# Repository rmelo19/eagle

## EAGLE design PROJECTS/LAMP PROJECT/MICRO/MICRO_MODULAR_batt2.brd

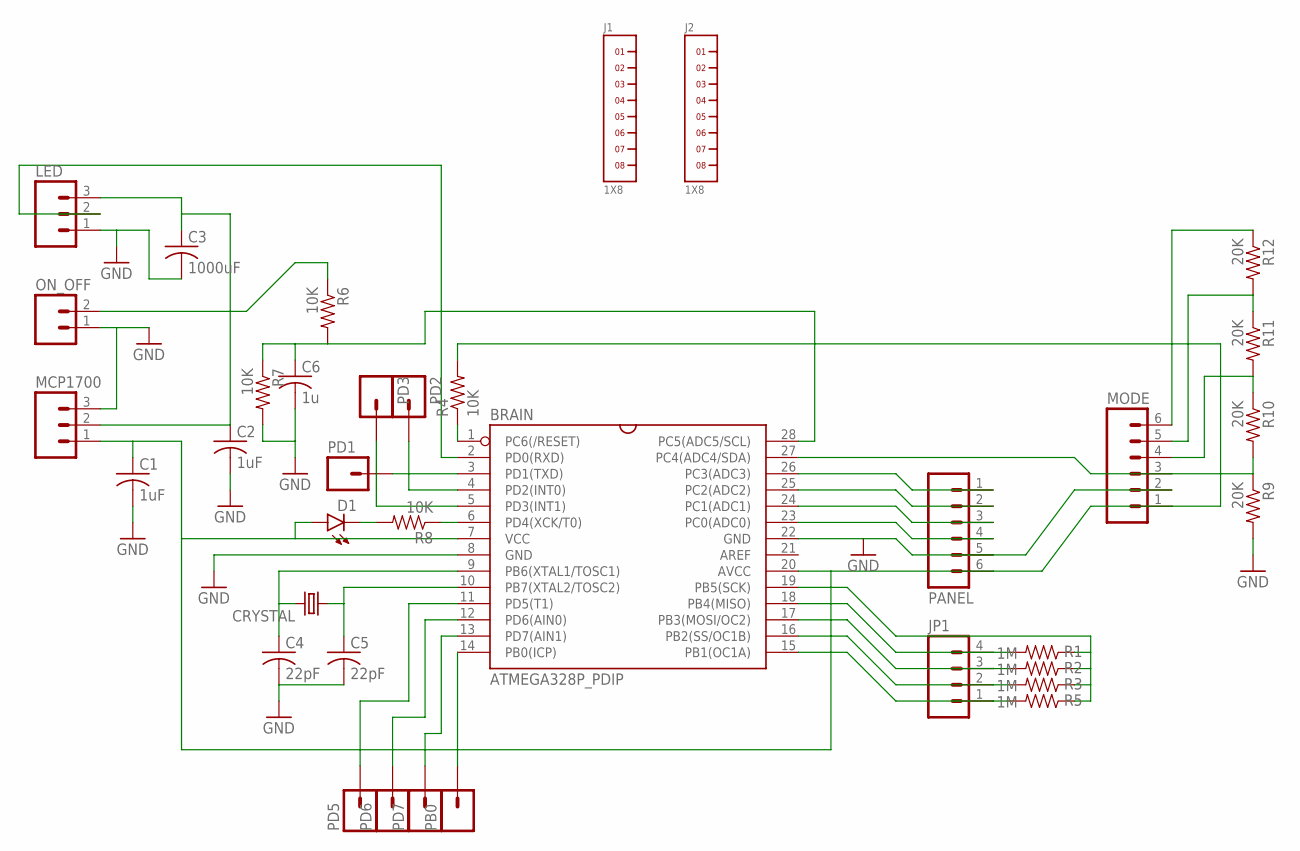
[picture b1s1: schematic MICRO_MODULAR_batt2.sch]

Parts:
BRAIN: ATMEGA328P_PDIP; DIL-28-3
C1, C2: 1uF; C050-025X075
C3: 1000uF; C050-075X075
C4, C5: 22pF; C025-024X044
C6: 1u; C050-025X075
CRYSTAL: CRYSTALHC49US; HC49US
D1: LED3MM
J1, J2: 1X8
JP1: M04PTH; 1X04
LED: M03PTH; 1X03
MCP1700: M03PTH; 1X03
MODE: M06SILK_FEMALE_PTH; 1X06
ON_OFF: M02PTH; 1X02
PANEL: M06NO_SILK_FEMALE_PTH; 1X06_NO_SILK
PB0: M01PTH; 1X01
PD1, PD2, PD3, PD5, PD6, PD7: M01PTH; 1X01
R1, R2, R3, R5: 1M; AXIAL-0.3
R4, R6, R7, R8: 10K; AXIAL-0.3
R9, R10, R11, R12: 20K; AXIAL-0.3

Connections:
BLUE_BRAIN: BRAIN.25 (PC2(ADC2)), PANEL.2
GND: BRAIN.8 (GND), BRAIN.22 (GND), C1.2, C2.2, C3.2, C4.2, C5.2, C6.2, LED.1, MCP1700.3, MODE.2, ON_OFF.1, PANEL.5, R7.P$2 (2), R9.P$2 (2)
GREEN_BRAIN: BRAIN.24 (PC1(ADC1)), PANEL.3
LEDS_BRAIN: BRAIN.2 (PD0(RXD)), LED.2
unnamed: BRAIN.28 (PC5(ADC5/SCL)), C6.1, R6.P$2 (2), R7.P$1 (1)
unnamed: BRAIN.15 (PB1(OC1A)), JP1.1, R5.P$2 (2)
unnamed: BRAIN.16 (PB2(SS/OC1B)), JP1.2, R3.P$2 (2)
unnamed: BRAIN.17 (PB3(MOSI/OC2)), JP1.3, R2.P$2 (2)
unnamed: BRAIN.18 (PB4(MISO)), JP1.4, R1.P$2 (2)
unnamed: BRAIN.19 (PB5(SCK)), R1.P$1 (1), R2.P$1 (1), R3.P$1 (1), R5.P$1 (1)
unnamed: BRAIN.9 (PB6(XTAL1/TOSC1)), C4.1, CRYSTAL.2
unnamed: BRAIN.10 (PB7(XTAL2/TOSC2)), C5.1, CRYSTAL.1
unnamed: BRAIN.5 (PD3(INT1)), PD3.1
unnamed: D1.K (C), R8.P$2 (2)
unnamed: BRAIN.6 (PD4(XCK/T0)), R8.P$1 (1)
unnamed: BRAIN.4 (PD2(INT0)), PD2.1
unnamed: BRAIN.27 (PC4(ADC4/SDA)), MODE.3, R9.P$1 (1), R10.P$2 (2)
unnamed: BRAIN.12 (PD6(AIN0)), PD6.1
unnamed: BRAIN.13 (PD7(AIN1)), PD7.1
unnamed: BRAIN.14 (PB0(ICP)), PB0.1
unnamed: BRAIN.3 (PD1(TXD)), PD1.1
unnamed: BRAIN.11 (PD5(T1)), PD5.1
unnamed: MODE.6, R12.P$1 (1)
unnamed: MODE.5, R11.P$1 (1), R12.P$2 (2)
unnamed: MODE.4, R10.P$1 (1), R11.P$2 (2)
RED_BRAIN: BRAIN.26 (PC3(ADC3)), PANEL.1
RST: BRAIN.1 (PC6(/RESET)), R4.P$1 (1)
SPEED_BRAIN: BRAIN.23 (PC0(ADC0)), PANEL.4
SWITCH_BRAIN: C2.1, C3.1, LED.3, MCP1700.2, ON_OFF.2, R6.P$1 (1)
V_5V: BRAIN.7 (VCC), BRAIN.20 (AVCC), C1.1, D1.A, MCP1700.1, MODE.1, PANEL.6, R4.P$2 (2)

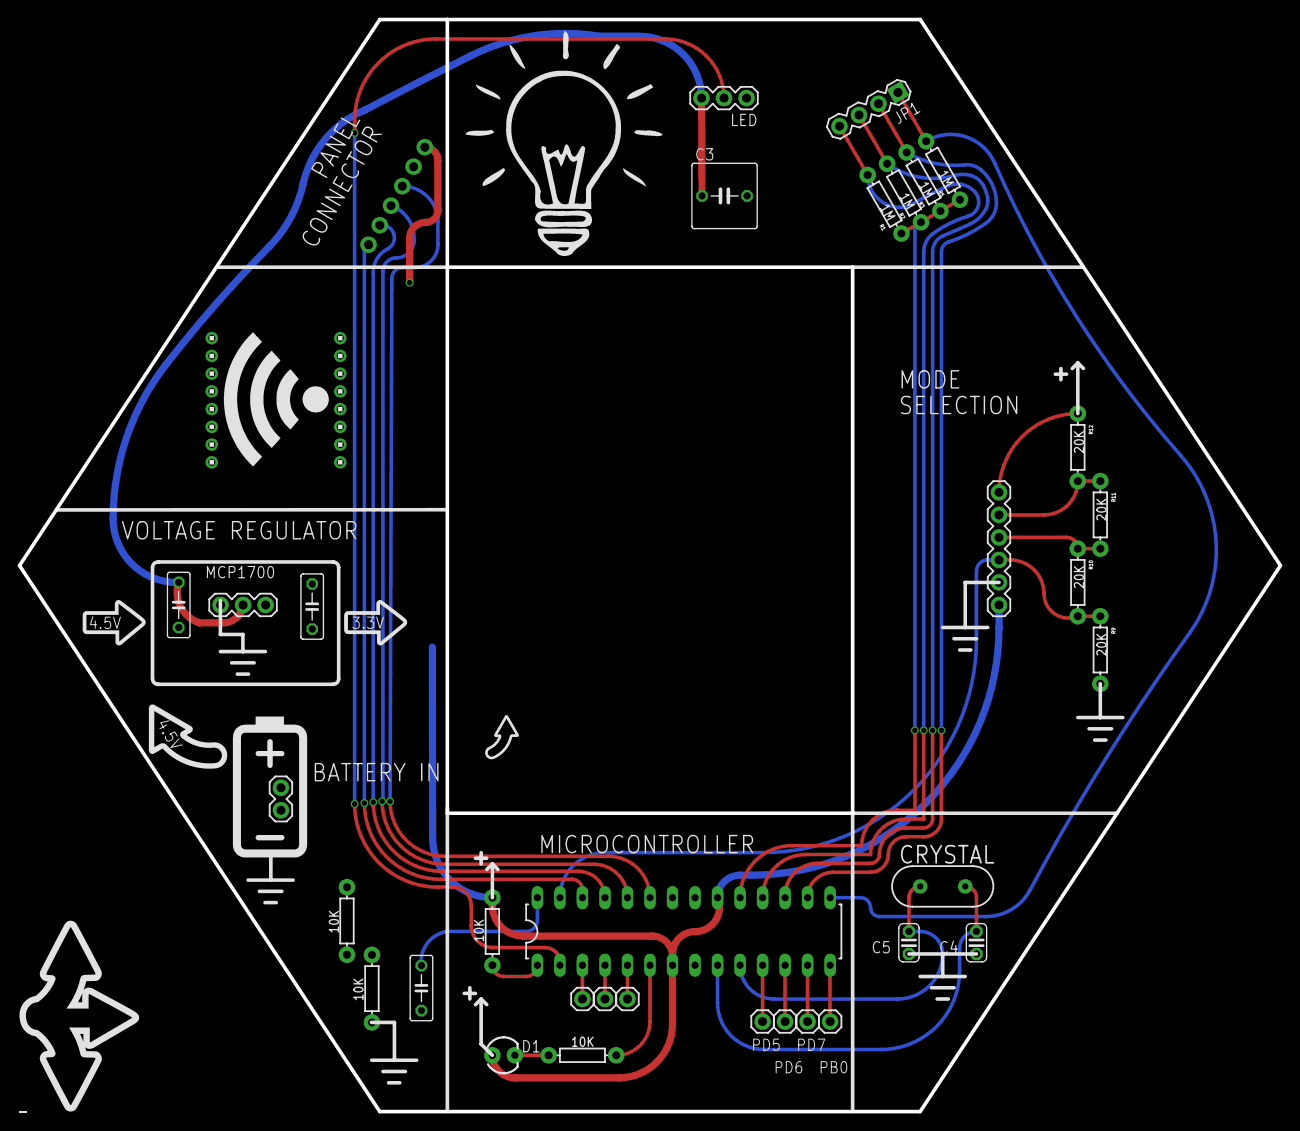
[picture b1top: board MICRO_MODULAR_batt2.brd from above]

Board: 2 copper layers, 142.2 x 123.2 mm, 36 parts (0 on the bottom side), 30 nets.

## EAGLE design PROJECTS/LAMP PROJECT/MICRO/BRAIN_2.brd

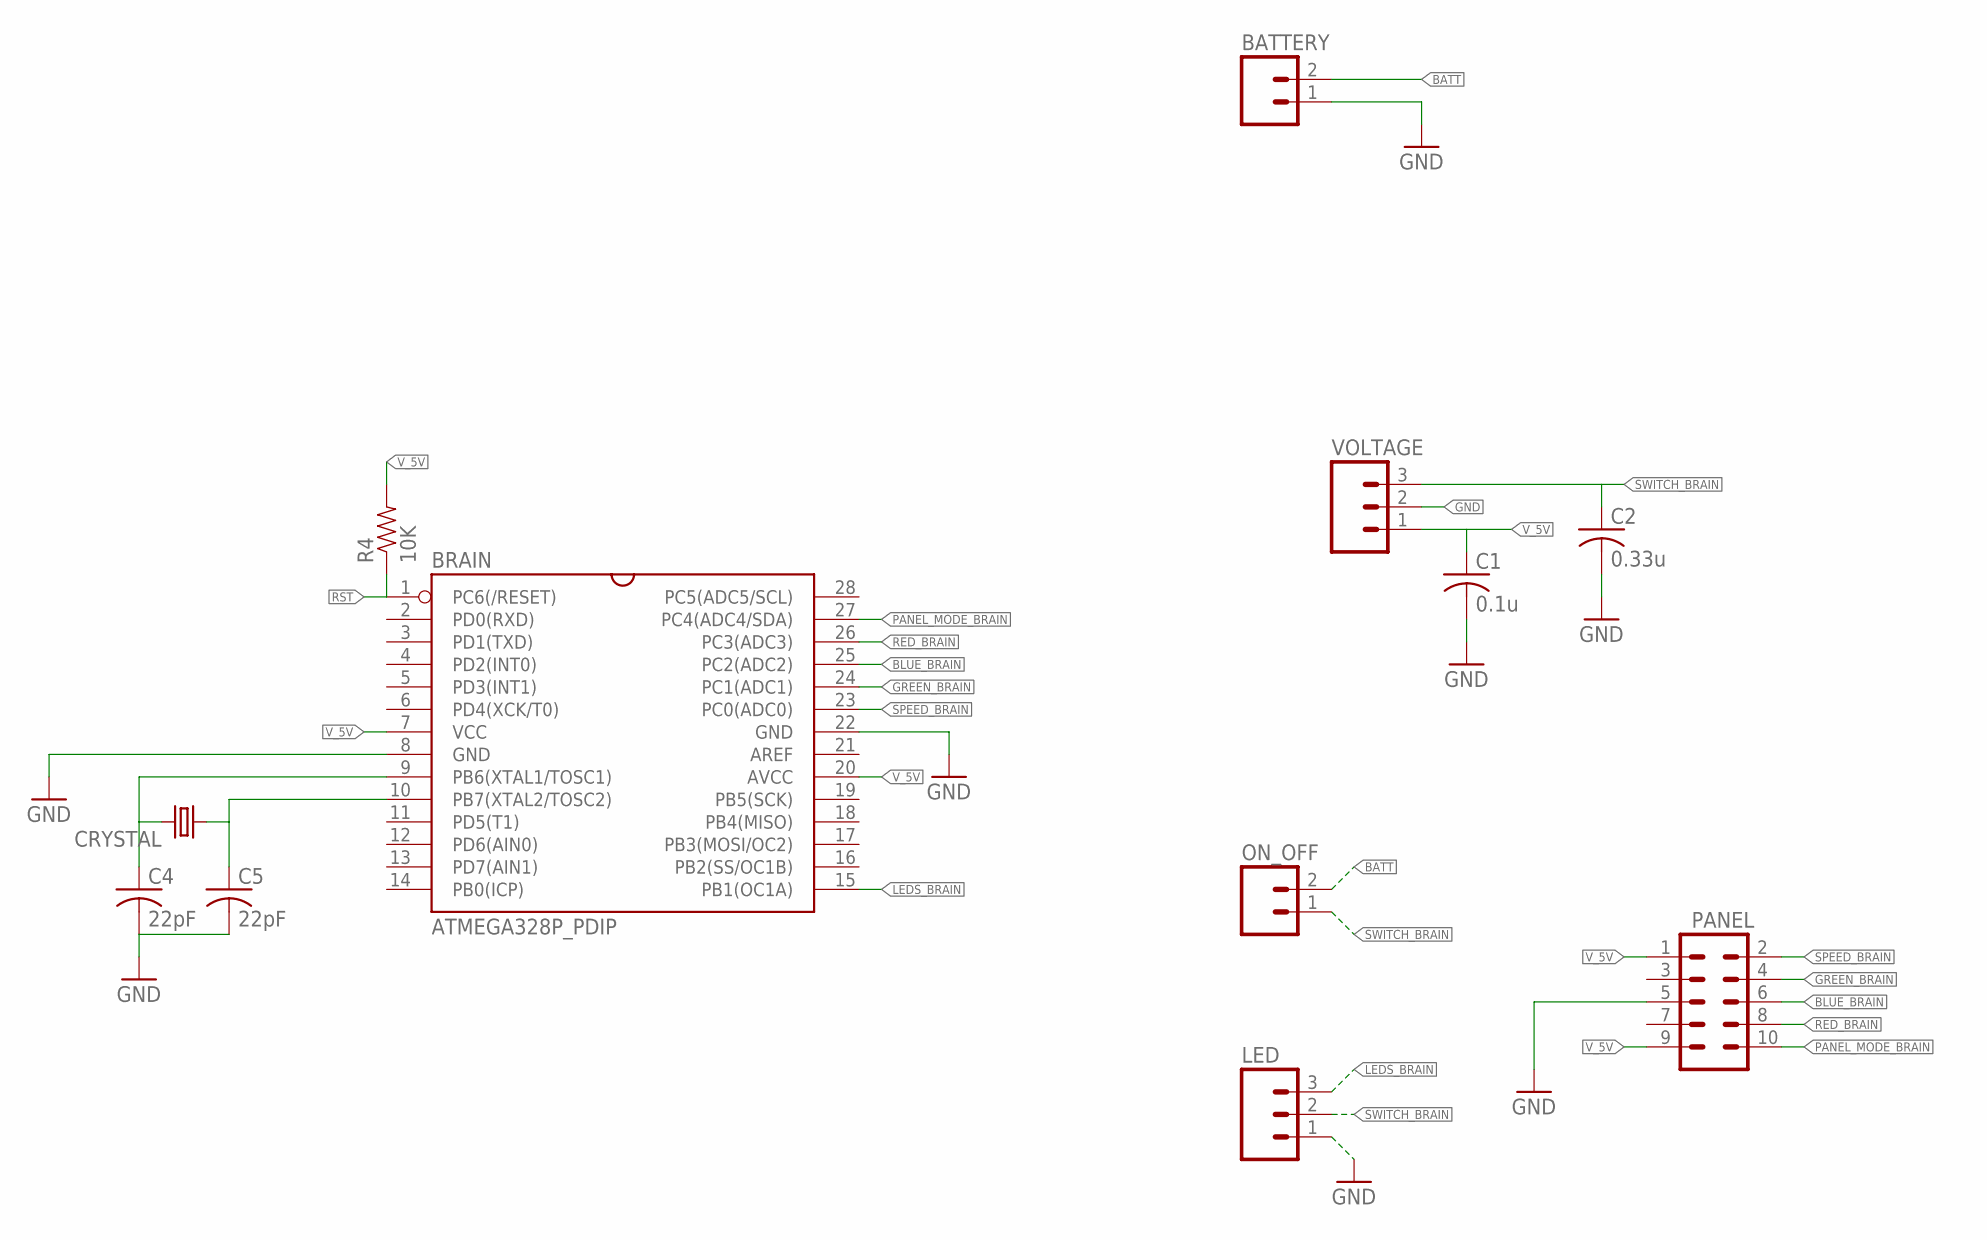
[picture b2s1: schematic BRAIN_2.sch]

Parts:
BATTERY: M02PTH; 1X02
BRAIN: ATMEGA328P_PDIP; DIL-28-3
C1: 0.1u; C025-025X050
C2: 0.33u; C025-025X050
C4, C5: 22pF; C025-024X044
CRYSTAL: CRYSTALHC49US; HC49US
LED: M03JST-PTH; JST-3-PTH
ON_OFF: M02-JST-2-PTH-NO_SILK; JST-2-PTH-NS
PANEL: M05X2SHD; 2X5-SHROUDED
R4: 10K; 1206
VOLTAGE: M03PTH; 1X03

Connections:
BATT: BATTERY.2, ON_OFF.2
BLUE_BRAIN: BRAIN.25 (PC2(ADC2)), PANEL.6
GND: BATTERY.1, BRAIN.8 (GND), BRAIN.22 (GND), C1.2, C2.2, C4.2, C5.2, LED.1, PANEL.5, VOLTAGE.2
GREEN_BRAIN: BRAIN.24 (PC1(ADC1)), PANEL.4
LEDS_BRAIN: BRAIN.15 (PB1(OC1A)), LED.3
unnamed: BRAIN.9 (PB6(XTAL1/TOSC1)), C4.1, CRYSTAL.2
unnamed: BRAIN.10 (PB7(XTAL2/TOSC2)), C5.1, CRYSTAL.1
PANEL_MODE_BRAIN: BRAIN.27 (PC4(ADC4/SDA)), PANEL.10
RED_BRAIN: BRAIN.26 (PC3(ADC3)), PANEL.8
RST: BRAIN.1 (PC6(/RESET)), R4.1
SPEED_BRAIN: BRAIN.23 (PC0(ADC0)), PANEL.2
SWITCH_BRAIN: C2.1, LED.2, ON_OFF.1, VOLTAGE.3
V_5V: BRAIN.7 (VCC), BRAIN.20 (AVCC), C1.1, PANEL.1, PANEL.9, R4.2, VOLTAGE.1

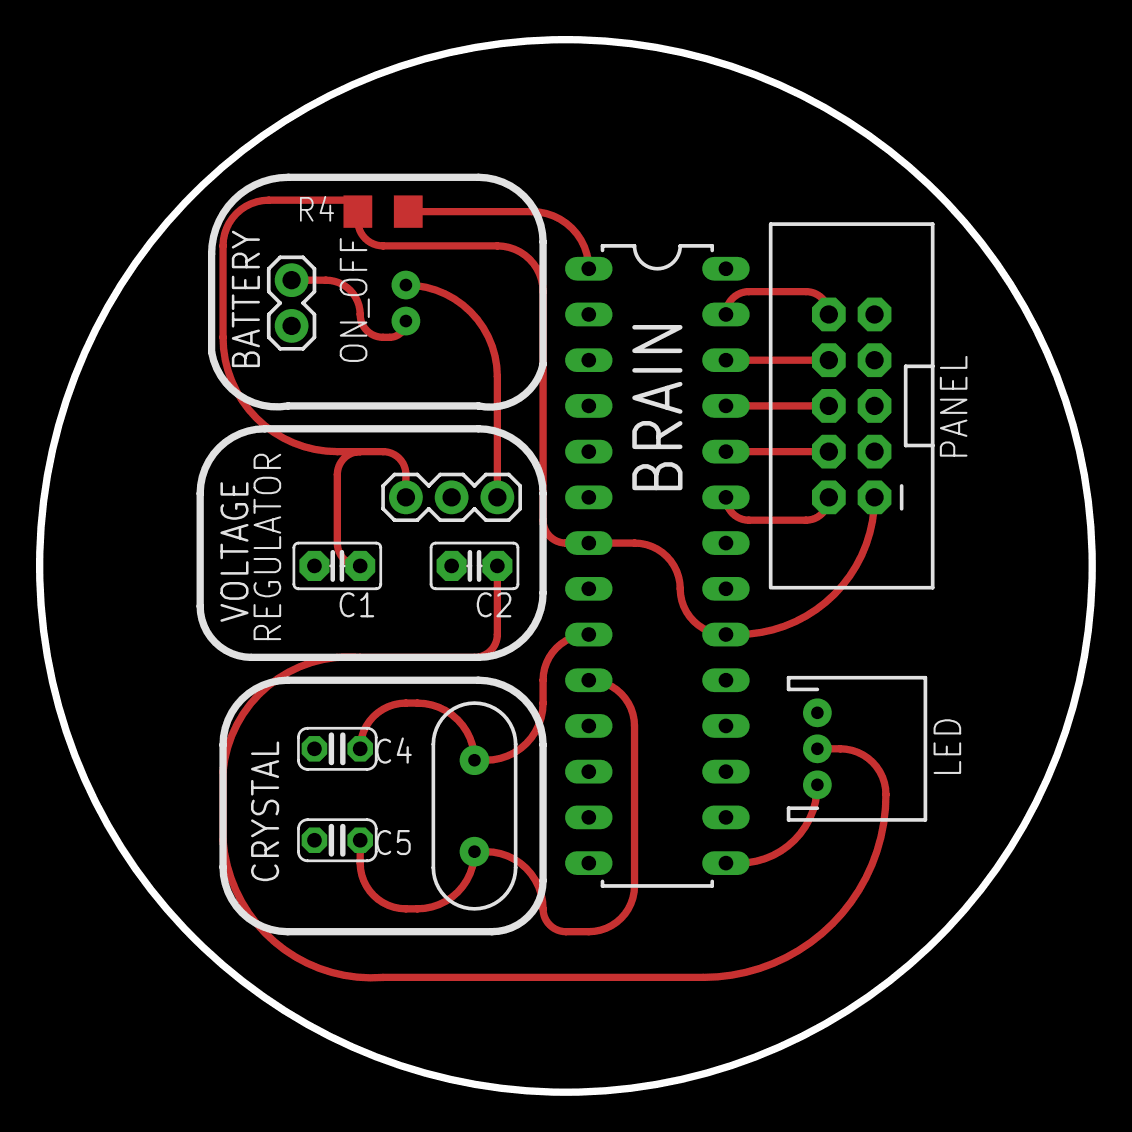
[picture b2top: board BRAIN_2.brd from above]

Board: 2 copper layers, 58.5 x 58.5 mm, 12 parts (0 on the bottom side), 13 nets.

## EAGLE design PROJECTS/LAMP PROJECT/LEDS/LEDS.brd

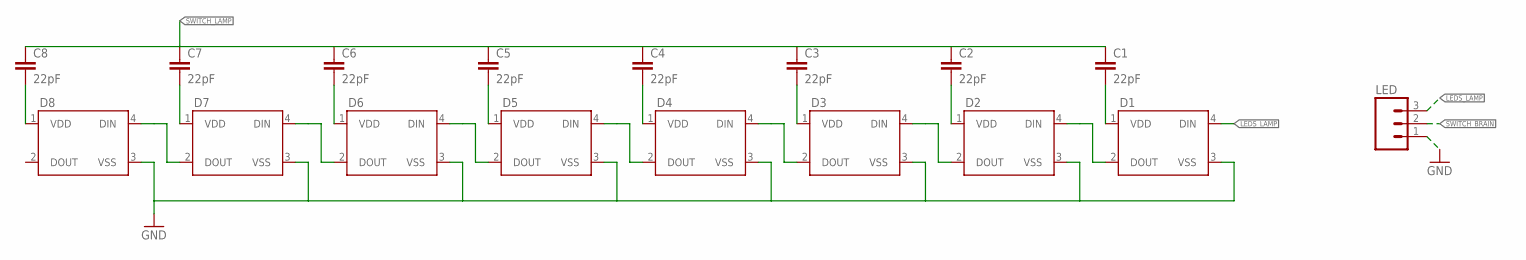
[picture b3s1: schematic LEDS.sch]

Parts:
C1, C2, C3, C4, C5, C6, C7, C8: 22pF; 1206
D1, D2, D3, D4, D5, D6, D7, D8: WS2812B
LED: M03JST-PTH; JST-3-PTH

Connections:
GND: D1.3 (VSS), D2.3 (VSS), D3.3 (VSS), D4.3 (VSS), D5.3 (VSS), D6.3 (VSS), D7.3 (VSS), D8.3 (VSS), LED.1
LEDS_LAMP: D1.4 (DIN), LED.3
unnamed: C1.2, D1.1 (VDD)
unnamed: C2.2, D2.1 (VDD)
unnamed: C3.2, D3.1 (VDD)
unnamed: C4.2, D4.1 (VDD)
unnamed: C5.2, D5.1 (VDD)
unnamed: C6.2, D6.1 (VDD)
unnamed: C7.2, D7.1 (VDD)
unnamed: C8.2, D8.1 (VDD)
SWITCH_BRAIN: LED.2
SWITCH_LAMP: C1.1, C2.1, C3.1, C4.1, C5.1, C6.1, C7.1, C8.1

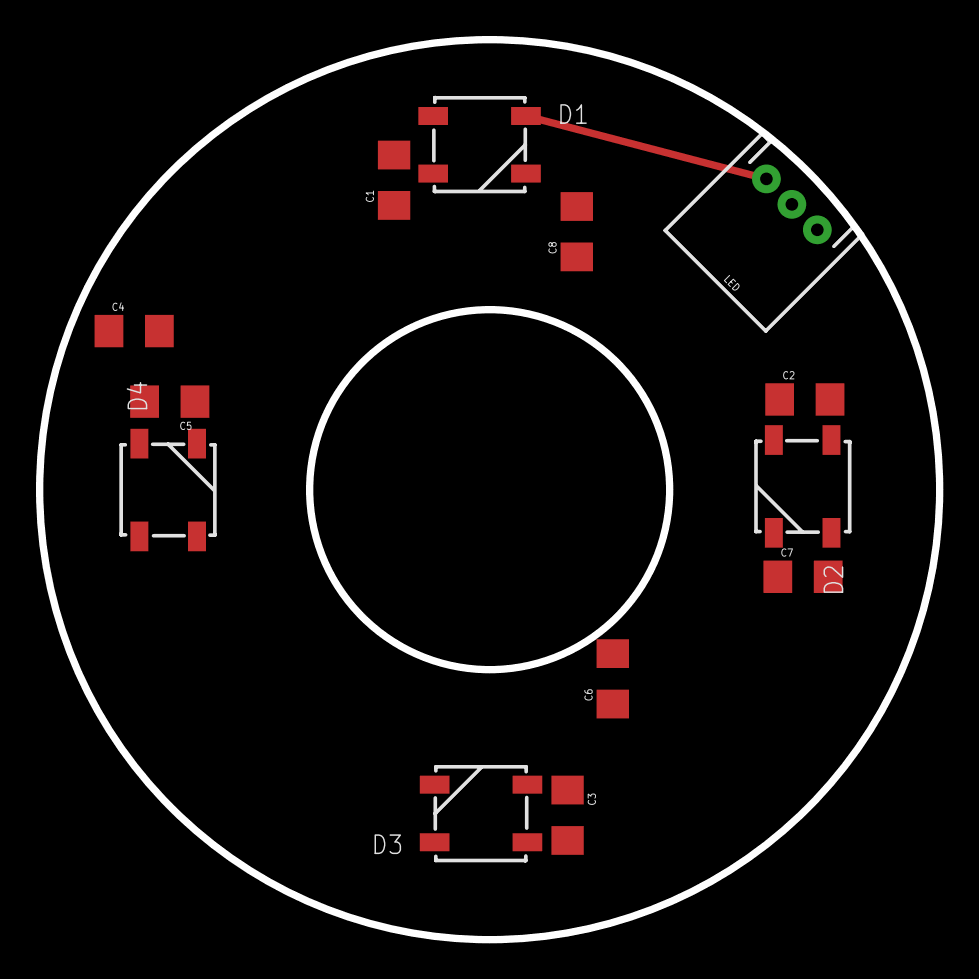
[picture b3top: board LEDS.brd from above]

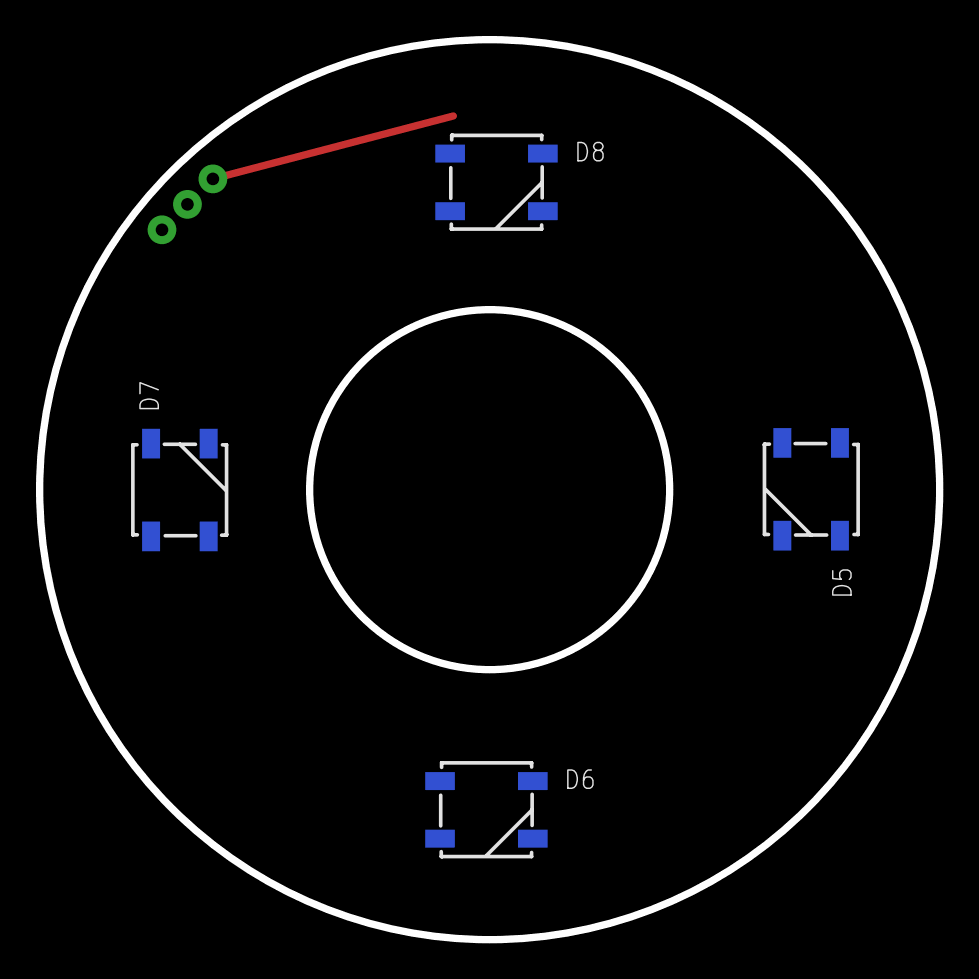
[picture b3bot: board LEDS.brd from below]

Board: 2 copper layers, 50.0 x 50.0 mm, 17 parts (4 on the bottom side), 11 nets.

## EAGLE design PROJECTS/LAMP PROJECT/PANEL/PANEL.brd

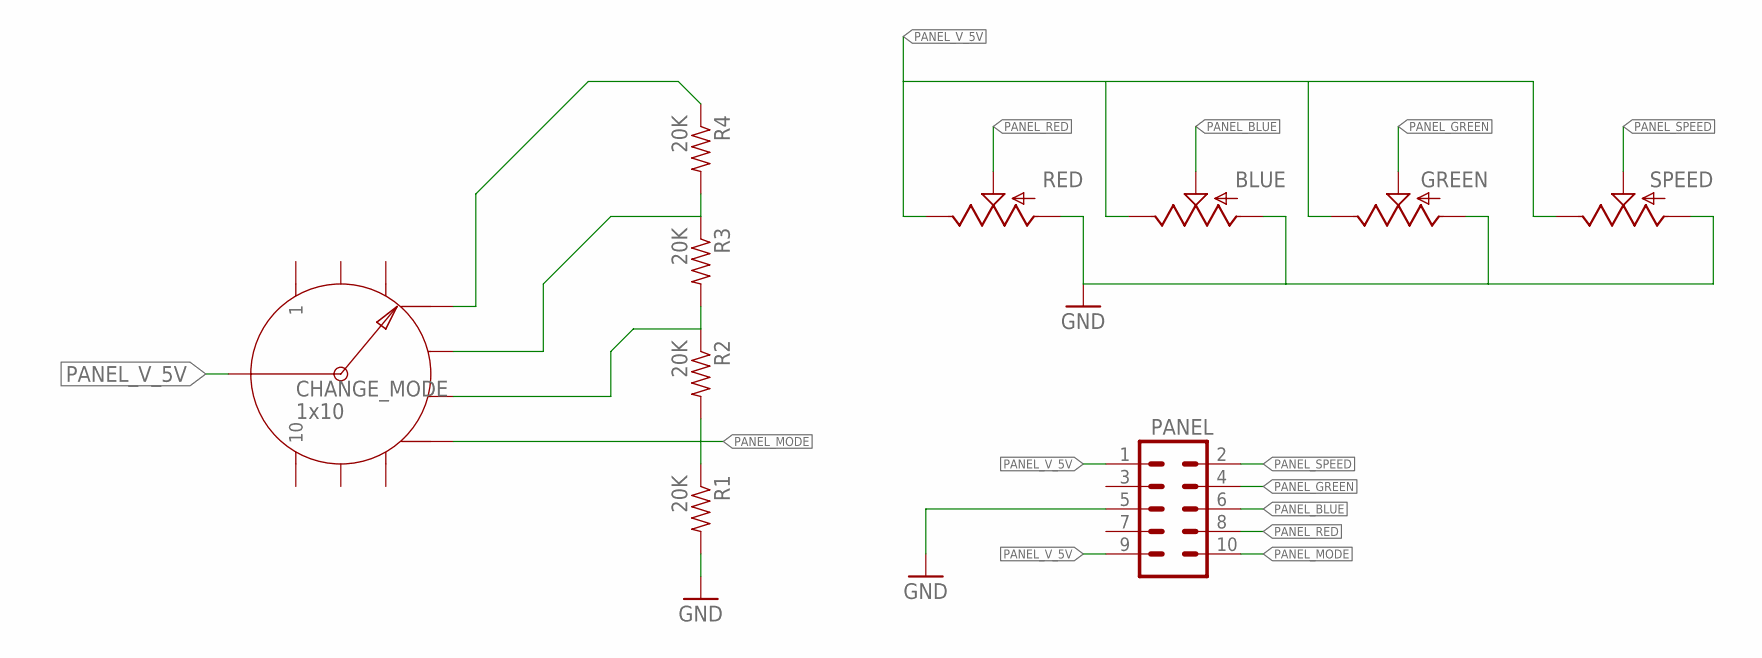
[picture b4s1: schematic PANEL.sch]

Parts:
BLUE: POT-RV16AF-20; POT_ALPHA_RV16AF-20
CHANGE_MODE: 1x10; ROTARY_SWITCH_1X10
GREEN: POT-RV16AF-20; POT_ALPHA_RV16AF-20
PANEL: M05X2SHD; 2X5-SHROUDED
R1, R2, R3, R4: 20K; 1206
RED: POT-RV16AF-20; POT_ALPHA_RV16AF-20
SPEED: POT-RV16AF-20; POT_ALPHA_RV16AF-20

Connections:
GND: BLUE.1 (A), GREEN.1 (A), PANEL.5, R1.2, RED.1 (A), SPEED.1 (A)
unnamed: CHANGE_MODE.4, R4.1
unnamed: CHANGE_MODE.5, R3.1, R4.2
unnamed: CHANGE_MODE.6, R2.1, R3.2
PANEL_BLUE: BLUE.2 (S), PANEL.6
PANEL_GREEN: GREEN.2 (S), PANEL.4
PANEL_MODE: CHANGE_MODE.7, PANEL.10, R1.1, R2.2
PANEL_RED: PANEL.8, RED.2 (S)
PANEL_SPEED: PANEL.2, SPEED.2 (S)
PANEL_V_5V: BLUE.3 (E), CHANGE_MODE.COMMON, GREEN.3 (E), PANEL.1, PANEL.9, RED.3 (E), SPEED.3 (E)

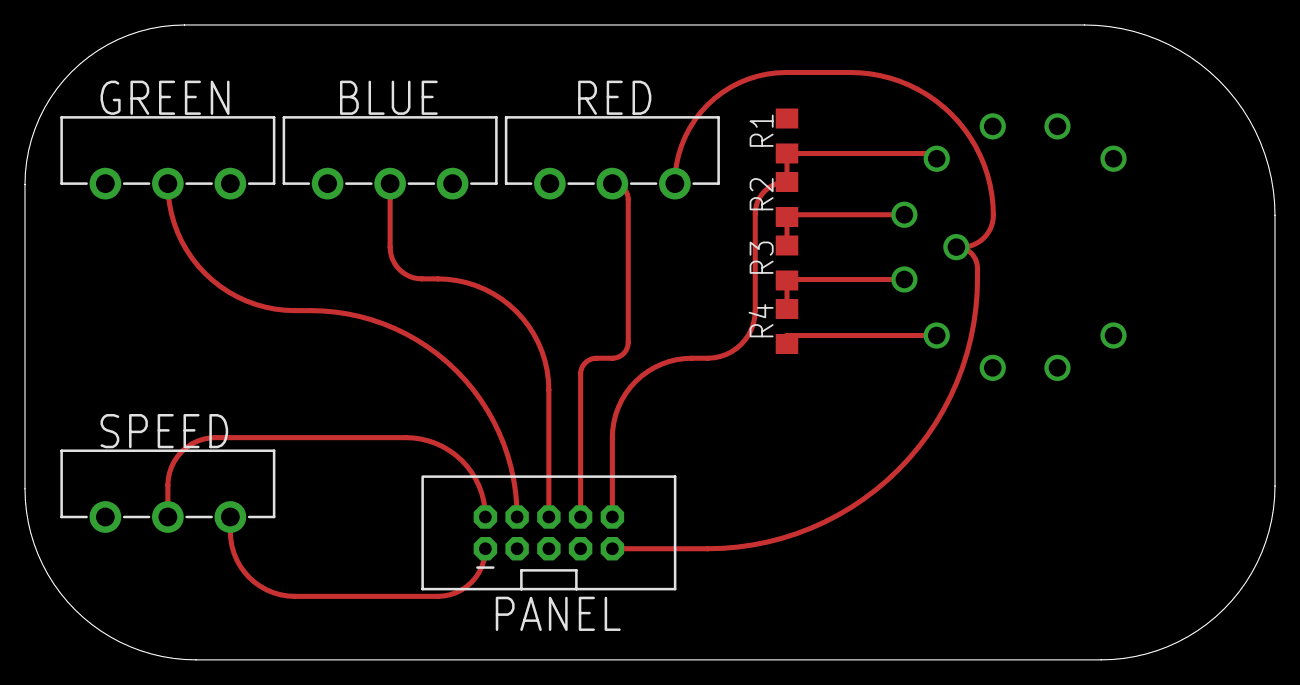
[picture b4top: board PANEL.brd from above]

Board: 2 copper layers, 100.0 x 50.8 mm, 10 parts (0 on the bottom side), 10 nets.

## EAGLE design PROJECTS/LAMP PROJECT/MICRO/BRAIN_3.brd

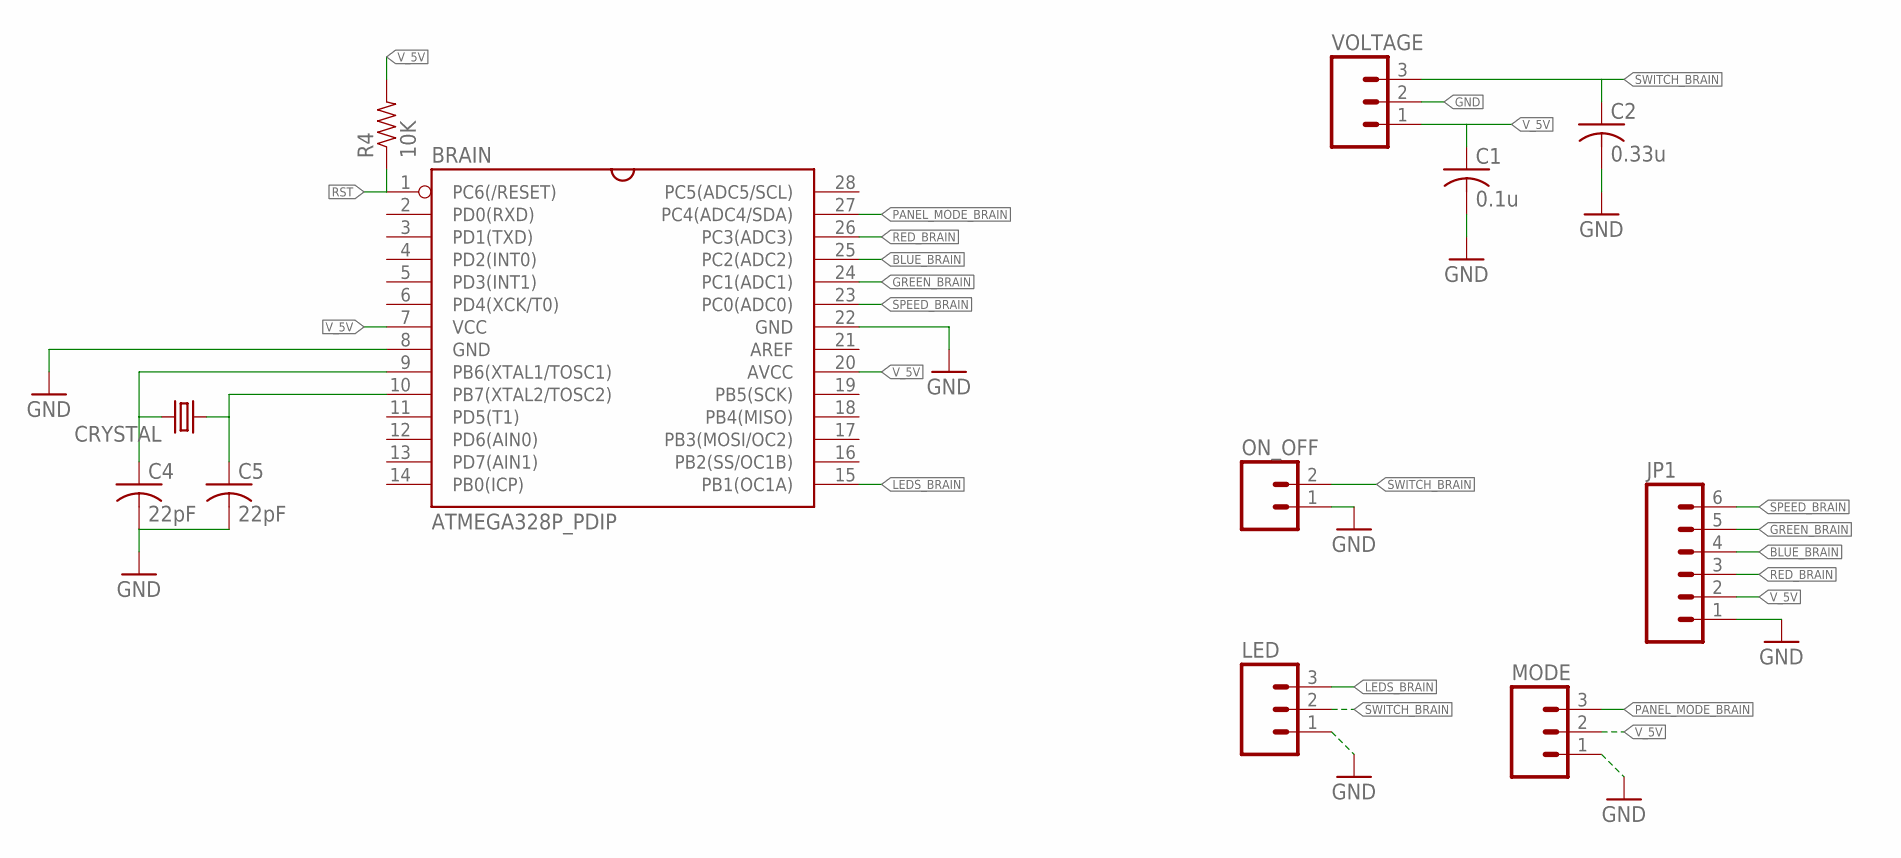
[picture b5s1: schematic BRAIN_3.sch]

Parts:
BRAIN: ATMEGA328P_PDIP; DIL-28-3
C1: 0.1u; C025-025X050
C2: 0.33u; C025-025X050
C4, C5: 22pF; C025-024X044
CRYSTAL: CRYSTALHC49US; HC49US
JP1: M06NO_SILK_FEMALE_PTH; 1X06_NO_SILK
LED: M03PTH; 1X03
MODE: M03PTH; 1X03
ON_OFF: M02PTH; 1X02
R4: 10K; AXIAL-0.3
VOLTAGE: M03PTH; 1X03

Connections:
BLUE_BRAIN: BRAIN.25 (PC2(ADC2)), JP1.4
GND: BRAIN.8 (GND), BRAIN.22 (GND), C1.2, C2.2, C4.2, C5.2, JP1.1, LED.1, MODE.1, ON_OFF.1, VOLTAGE.2
GREEN_BRAIN: BRAIN.24 (PC1(ADC1)), JP1.5
LEDS_BRAIN: BRAIN.15 (PB1(OC1A)), LED.3
unnamed: BRAIN.9 (PB6(XTAL1/TOSC1)), C4.1, CRYSTAL.2
unnamed: BRAIN.10 (PB7(XTAL2/TOSC2)), C5.1, CRYSTAL.1
PANEL_MODE_BRAIN: BRAIN.27 (PC4(ADC4/SDA)), MODE.3
RED_BRAIN: BRAIN.26 (PC3(ADC3)), JP1.3
RST: BRAIN.1 (PC6(/RESET)), R4.P$1 (1)
SPEED_BRAIN: BRAIN.23 (PC0(ADC0)), JP1.6
SWITCH_BRAIN: C2.1, LED.2, ON_OFF.2, VOLTAGE.3
V_5V: BRAIN.7 (VCC), BRAIN.20 (AVCC), C1.1, JP1.2, MODE.2, R4.P$2 (2), VOLTAGE.1

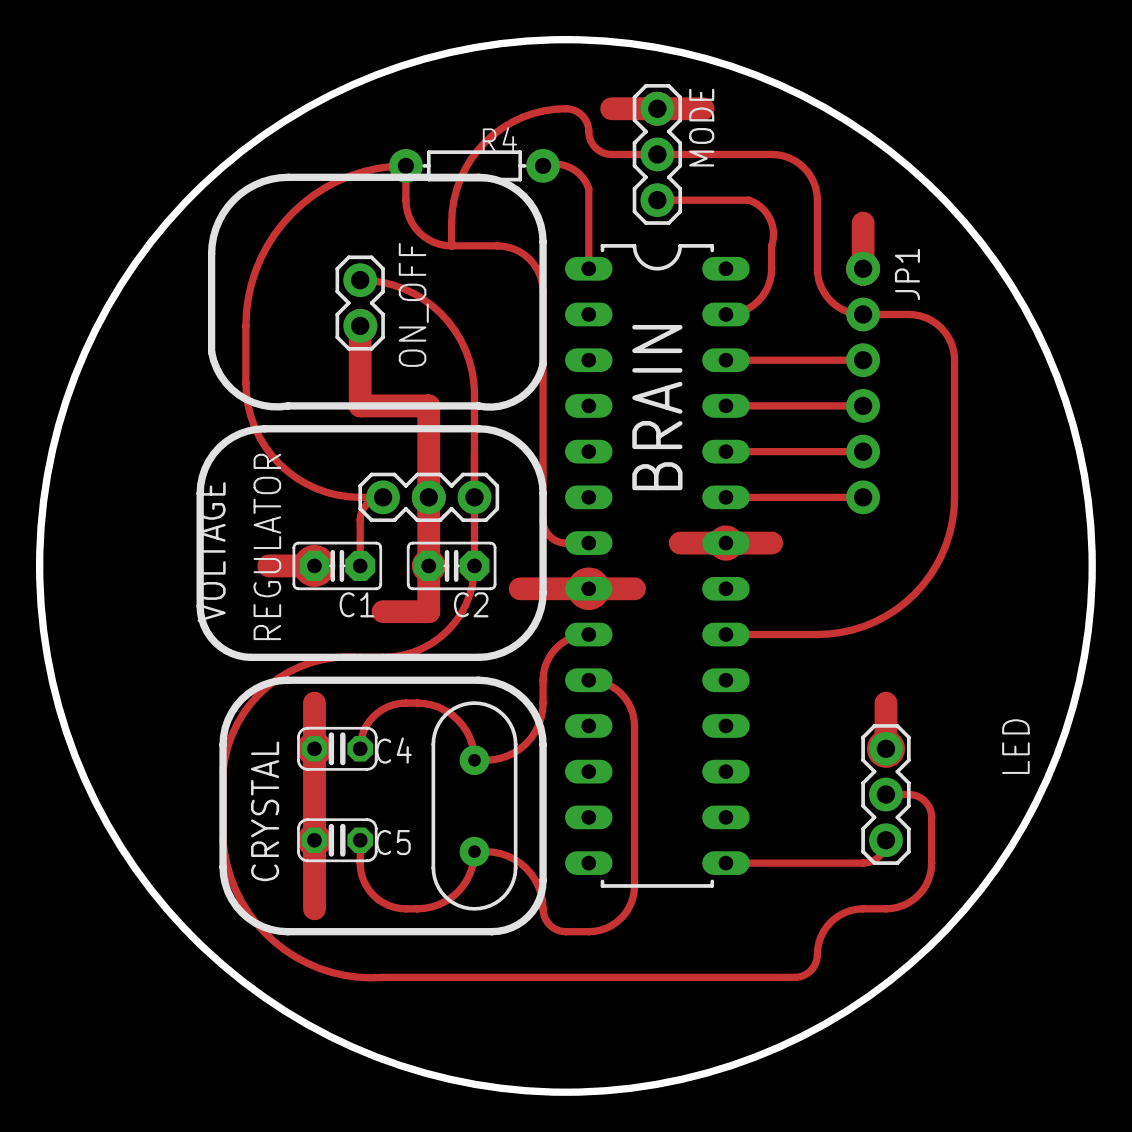
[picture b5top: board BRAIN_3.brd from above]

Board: 2 copper layers, 58.5 x 58.5 mm, 12 parts (0 on the bottom side), 12 nets.

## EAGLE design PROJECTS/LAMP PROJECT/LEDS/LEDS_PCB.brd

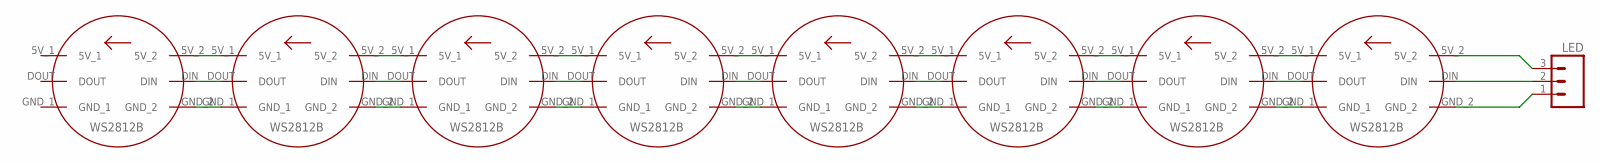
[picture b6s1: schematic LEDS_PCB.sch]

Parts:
LED: M03PTH; 1X03
U$1, U$2, U$3, U$4, U$5, U$6, U$7, U$8: WS2812B_LED; CIRCLE_PCB

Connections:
unnamed: U$1.5V_1, U$2.5V_2
unnamed: U$1.DOUT, U$2.DIN
unnamed: U$1.GND_1, U$2.GND_2
unnamed: U$2.5V_1, U$3.5V_2
unnamed: U$2.DOUT, U$3.DIN
unnamed: U$2.GND_1, U$3.GND_2
unnamed: U$3.5V_1, U$4.5V_2
unnamed: U$3.DOUT, U$4.DIN
unnamed: U$3.GND_1, U$4.GND_2
unnamed: U$5.5V_1, U$6.5V_2
unnamed: U$5.DOUT, U$6.DIN
unnamed: U$5.GND_1, U$6.GND_2
unnamed: U$6.5V_1, U$7.5V_2
unnamed: U$6.DOUT, U$7.DIN
unnamed: U$6.GND_1, U$7.GND_2
unnamed: U$7.5V_1, U$8.5V_2
unnamed: U$7.DOUT, U$8.DIN
unnamed: U$7.GND_1, U$8.GND_2
unnamed: U$4.5V_1, U$5.5V_2
unnamed: U$4.DOUT, U$5.DIN
unnamed: U$4.GND_1, U$5.GND_2
unnamed: LED.1, U$1.GND_2
unnamed: LED.2, U$1.DIN
unnamed: LED.3, U$1.5V_2

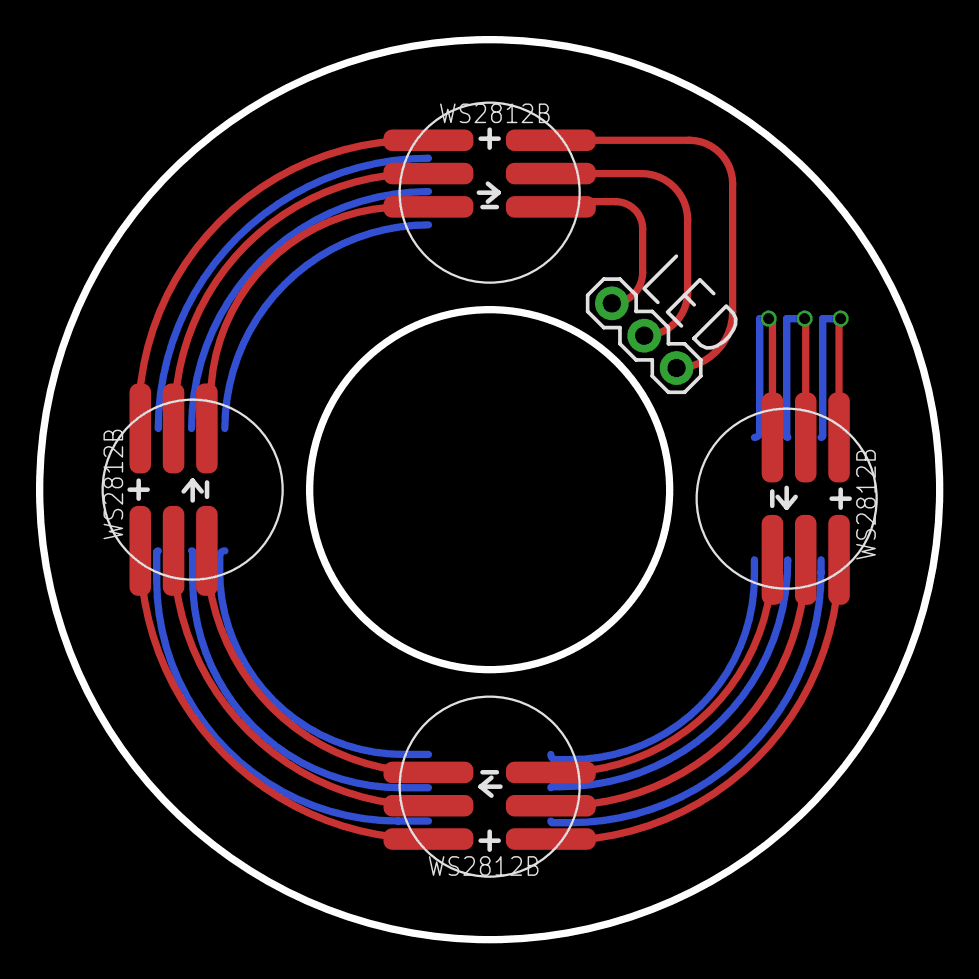
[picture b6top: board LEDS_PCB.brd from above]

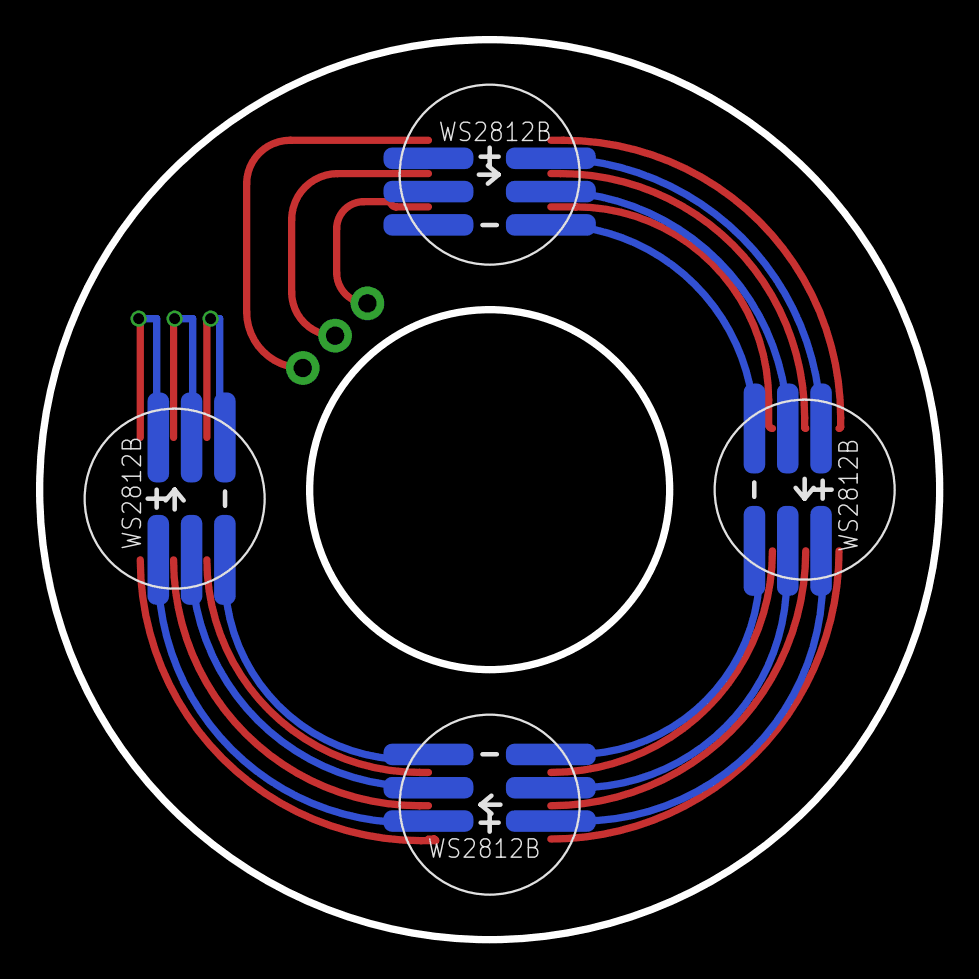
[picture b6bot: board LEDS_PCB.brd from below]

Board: 2 copper layers, 50.0 x 50.0 mm, 9 parts (4 on the bottom side), 24 nets.

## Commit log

2016-06-13 copying eagle files from previous repo
2016-06-17 small modifications in some projects
2016-06-20 updates to lamp project

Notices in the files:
parts and their libraries:
SparkFun-LED: Licensing: Creative Commons ShareAlike 4.0 International - https://creativecommons.org/licenses/by-sa/4.0
